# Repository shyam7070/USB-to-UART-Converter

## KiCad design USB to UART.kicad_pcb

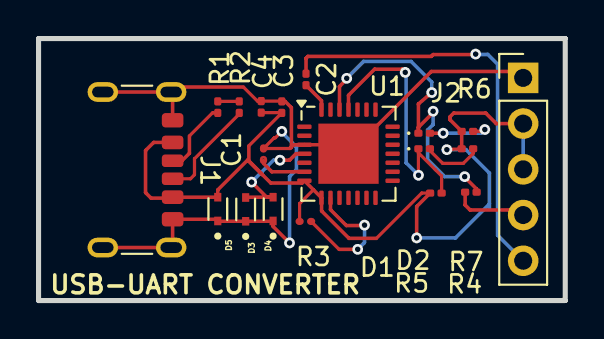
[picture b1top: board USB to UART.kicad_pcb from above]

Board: 2 copper layers, 29.3 x 14.6 mm, 19 parts (0 on the bottom side), 15 nets.

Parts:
C1, C2, C3, C4: 100nF; C_0201_0603Metric
D1, D2: LED; LED_0201_0603Metric
D3, D4, D5: LESD5D5.0CT1G; TVS_LESD5D5.0CT1G
J1: USB_C_Receptacle_USB2.0_16P; USB_C_Receptacle_GCT_USB4125-xx-x-0190_6P_TopMnt_Horizontal
J2: Conn_01x05_Pin; PinHeader_1x05_P2.54mm_Vertical
R1, R2: 5.1k; R_0201_0603Metric
R3: 10k; R_0201_0603Metric
R4, R5, R6, R7: 1K; R_0201_0603Metric
U1: CP2102N-Axx-xQFN28; QFN-28-1EP_5x5mm_P0.5mm_EP3.35x3.35mm

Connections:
/D+: D3.2, D4.2, U1.4 (D+)
/VBUS: C3.1, C4.1, D5.2, J1.A9 (VBUS), J1.B9 (VBUS), J2.2, J2.3, R3.1, R5.1, R6.1, R7.1, U1.7 (VREGIN), U1.8 (VBUS)
GND: C1.1, C3.2, C4.2, D3.1, D4.1, D5.1, J1.A12 (GND), J1.B12 (GND), J1.S1 (SHIELD), J2.1, U1.3 (GND), U1.29 (GND)
unnamed: D1.2 (A), R6.2
unnamed: D1.1 (K), R4.2, U1.26 (TXD)
unnamed: D2.2 (A), R7.2
unnamed: D2.1 (K), R5.2, U1.25 (RXD)
unnamed: J1.A5 (CC1), R1.1
unnamed: J1.B5 (CC2), R2.1
unnamed: J2.4, R4.1
unnamed: C2.2, J2.5
unnamed: R1.2, R2.2
unnamed: C1.2, U1.6 (VDD)
unnamed: C2.1, U1.28 (~DTR)
unnamed: R3.2, U1.9 (~RST)
